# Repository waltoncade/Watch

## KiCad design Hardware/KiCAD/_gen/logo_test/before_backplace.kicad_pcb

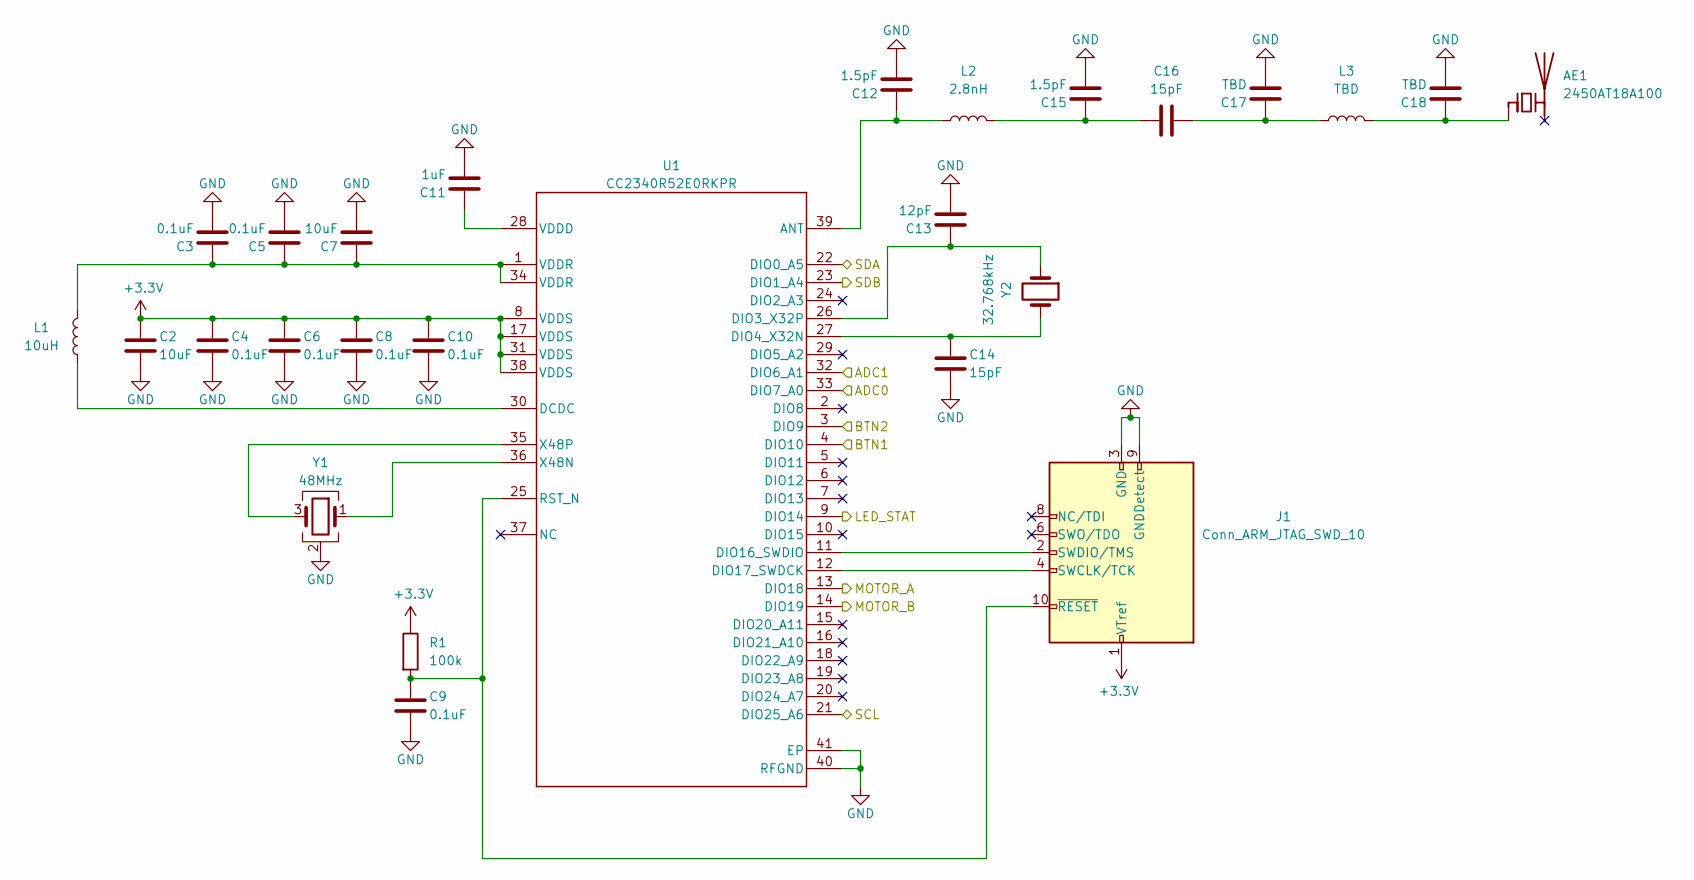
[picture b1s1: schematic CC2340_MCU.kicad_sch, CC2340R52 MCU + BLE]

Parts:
AE1: 2450AT18A100; Johanson_2450AT18x100; MPN Johanson 2450AT18A100 (placeholder, TBD)
C2, C7: 10uF; C_0402_1005Metric
C3, C4, C5, C6, C8, C9, C10: 0.1uF; C_0402_1005Metric
C11: 1uF; C_0402_1005Metric
C12, C15: 1.5pF; C_0402_1005Metric
C13: 12pF; C_0402_1005Metric
C14, C16: 15pF; C_0402_1005Metric
C17, C18: TBD; C_0402_1005Metric
J1: Conn_ARM_JTAG_SWD_10; PinHeader_2x05_P1.27mm_Vertical_SMD
L1: 10uH; L_0603_1608Metric; MPN MLZ1608N100LT000 (TI E2E-tested 0603 al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
L2: 2.8nH; L_0402_1005Metric
L3: TBD; L_0402_1005Metric
R1: 100k; R_0402_1005Metric
U1: CC2340R52E0RKPR; RKP0040B-IPC_B
Y1: 48MHz; Crystal_SMD_2016-4Pin_2.0x1.6mm; MPN TZ3908AAAO43
Y2: 32.768kHz; Crystal_SMD_2012-2Pin_2.0x1.2mm; MPN TBD (CL 6-12pF per SWRS272F CC2340R5 da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

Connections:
+3.3V: C2.1, C4.1, C6.1, C8.1, C10.1, J1.1 (VTref), R1.1, U1.8 (VDDS), U1.17 (VDDS), U1.31 (VDDS), U1.38 (VDDS); also elsewhere on the board
/ACC_INT: U1.20 (DIO24_A7); also elsewhere on the board
/LED_EN: U1.23 (DIO1_A4); also elsewhere on the board
/MCU/LED_STAT: U1.9 (DIO14); also elsewhere on the board
/MCU/MOTOR_A: U1.13 (DIO18); also elsewhere on the board
/MCU/MOTOR_B: U1.14 (DIO19); also elsewhere on the board
/SW1: U1.4 (DIO10); also elsewhere on the board
/SW2: U1.3 (DIO9); also elsewhere on the board
/bSense: U1.33 (DIO7_A0); also elsewhere on the board
/leds/SCL: U1.21 (DIO25_A6); also elsewhere on the board
/leds/SDA: U1.22 (DIO0_A5); also elsewhere on the board
/vLUX: U1.32 (DIO6_A1); also elsewhere on the board
GND: C2.2, C3.2, C4.2, C5.2, C6.2, C7.2, C8.2, C9.2, C10.2, C11.2, C12.2, C13.2, C14.2, C15.2, C17.2, C18.2, J1.3 (GND), J1.5 (GND), J1.9 (GNDDetect), U1.40 (RFGND), U1.41 (EP), Y1.2 (G), Y1.4 (G); also elsewhere on the board
unnamed: AE1.1 (FEED_1), C18.1, L3.2
unnamed: C3.1, C5.1, C7.1, L1.2, U1.1 (VDDR), U1.34 (VDDR)
unnamed: C15.1, C16.1, L2.2
unnamed: C16.2, C17.1, L3.1
unnamed 50: J1.4 (SWCLK/TCK), U1.12 (DIO17_SWDCK); also elsewhere on the board
unnamed 51: J1.2 (SWDIO/TMS), U1.11 (DIO16_SWDIO); also elsewhere on the board
unnamed: C12.1, L2.1, U1.39 (ANT)
unnamed: L1.1, U1.30 (DCDC)
unnamed: C13.1, U1.26 (DIO3_X32P), Y2.1
unnamed: C14.1, U1.27 (DIO4_X32N), Y2.2
unnamed: C11.1, U1.28 (VDDD)
unnamed: U1.36 (X48N), Y1.1
unnamed: U1.35 (X48P), Y1.3

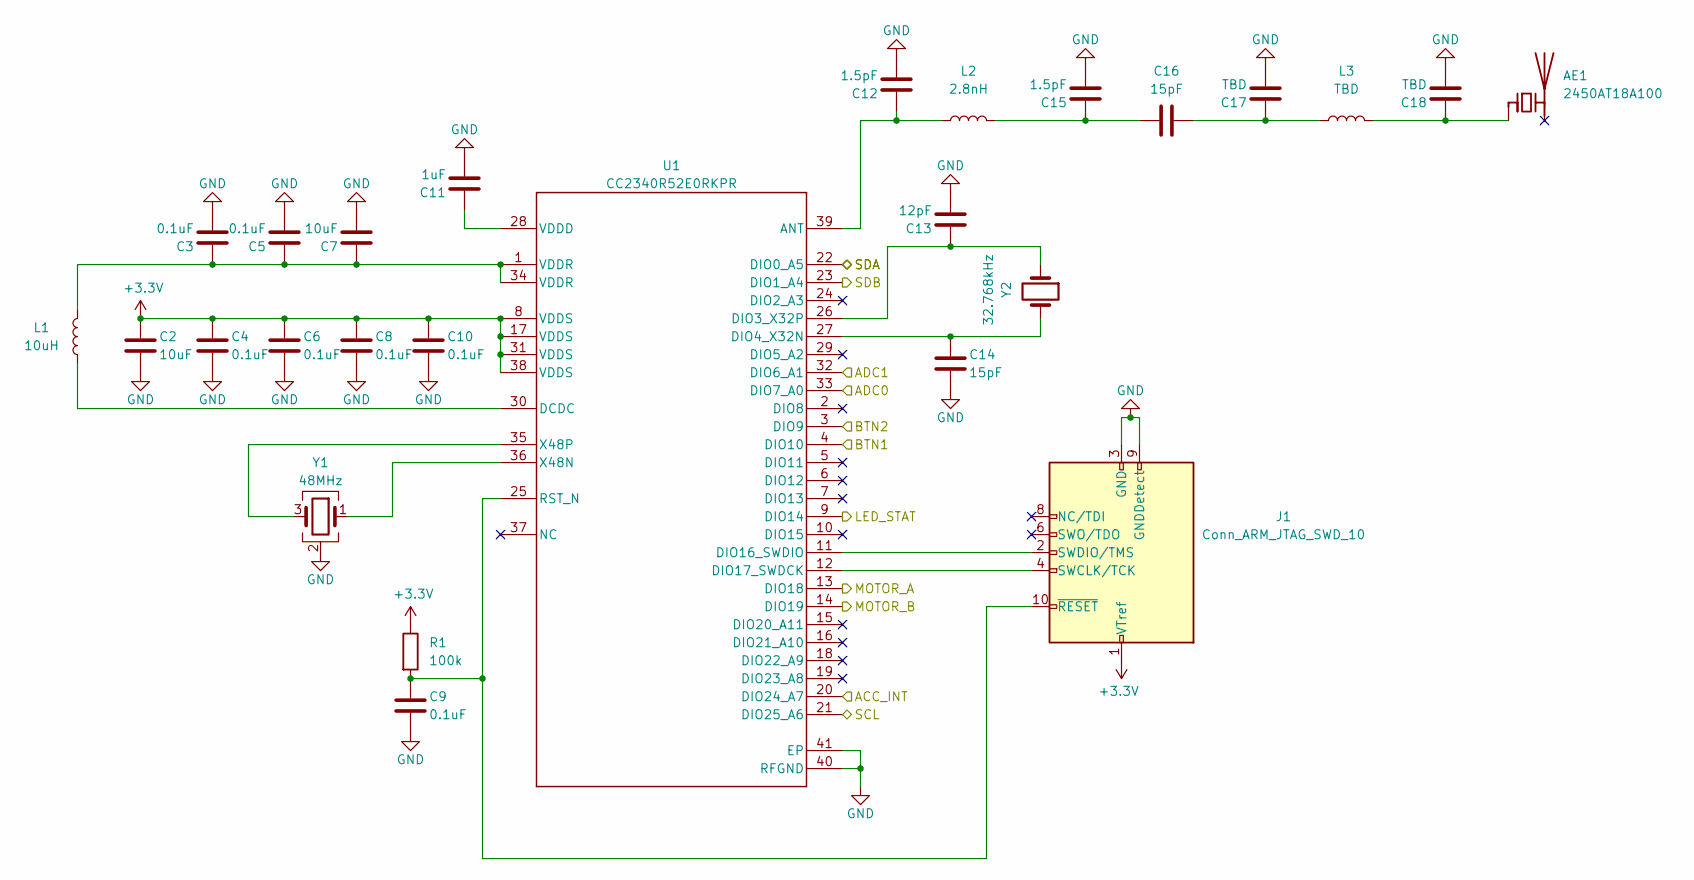
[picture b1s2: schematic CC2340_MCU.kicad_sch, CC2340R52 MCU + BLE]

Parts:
AE1: 2450AT18A100; Johanson_2450AT18x100; MPN Johanson 2450AT18A100 (placeholder, TBD)
C2, C7: 10uF; C_0402_1005Metric
C3, C4, C5, C6, C8, C9, C10: 0.1uF; C_0402_1005Metric
C11: 1uF; C_0402_1005Metric
C12, C15: 1.5pF; C_0402_1005Metric
C13: 12pF; C_0402_1005Metric
C14, C16: 15pF; C_0402_1005Metric
C17, C18: TBD; C_0402_1005Metric
J1: Conn_ARM_JTAG_SWD_10; PinHeader_2x05_P1.27mm_Vertical_SMD
L1: 10uH; L_0603_1608Metric; MPN MLZ1608N100LT000 (TI E2E-tested 0603 al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
L2: 2.8nH; L_0402_1005Metric
L3: TBD; L_0402_1005Metric
R1: 100k; R_0402_1005Metric
U1: CC2340R52E0RKPR; RKP0040B-IPC_B
Y1: 48MHz; Crystal_SMD_2016-4Pin_2.0x1.6mm; MPN TZ3908AAAO43
Y2: 32.768kHz; Crystal_SMD_2012-2Pin_2.0x1.2mm; MPN TBD (CL 6-12pF per SWRS272F CC2340R5 da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

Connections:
+3.3V: C2.1, C4.1, C6.1, C8.1, C10.1, J1.1 (VTref), R1.1, U1.8 (VDDS), U1.17 (VDDS), U1.31 (VDDS), U1.38 (VDDS); also elsewhere on the board
/ACC_INT: U1.20 (DIO24_A7); also elsewhere on the board
/LED_EN: U1.23 (DIO1_A4); also elsewhere on the board
/MCU/LED_STAT: U1.9 (DIO14); also elsewhere on the board
/MCU/MOTOR_A: U1.13 (DIO18); also elsewhere on the board
/MCU/MOTOR_B: U1.14 (DIO19); also elsewhere on the board
/SW1: U1.4 (DIO10); also elsewhere on the board
/SW2: U1.3 (DIO9); also elsewhere on the board
/bSense: U1.33 (DIO7_A0); also elsewhere on the board
/leds/SCL: U1.21 (DIO25_A6); also elsewhere on the board
/leds/SDA: U1.22 (DIO0_A5); also elsewhere on the board
/vLUX: U1.32 (DIO6_A1); also elsewhere on the board
GND: C2.2, C3.2, C4.2, C5.2, C6.2, C7.2, C8.2, C9.2, C10.2, C11.2, C12.2, C13.2, C14.2, C15.2, C17.2, C18.2, J1.3 (GND), J1.5 (GND), J1.9 (GNDDetect), U1.40 (RFGND), U1.41 (EP), Y1.2 (G), Y1.4 (G); also elsewhere on the board
unnamed: AE1.1 (FEED_1), C18.1, L3.2
unnamed: C3.1, C5.1, C7.1, L1.2, U1.1 (VDDR), U1.34 (VDDR)
unnamed: C15.1, C16.1, L2.2
unnamed: C16.2, C17.1, L3.1
unnamed 50: J1.4 (SWCLK/TCK), U1.12 (DIO17_SWDCK); also elsewhere on the board
unnamed 51: J1.2 (SWDIO/TMS), U1.11 (DIO16_SWDIO); also elsewhere on the board
unnamed: C12.1, L2.1, U1.39 (ANT)
unnamed: L1.1, U1.30 (DCDC)
unnamed: C13.1, U1.26 (DIO3_X32P), Y2.1
unnamed: C14.1, U1.27 (DIO4_X32N), Y2.2
unnamed: C11.1, U1.28 (VDDD)
unnamed: U1.36 (X48N), Y1.1
unnamed: U1.35 (X48P), Y1.3

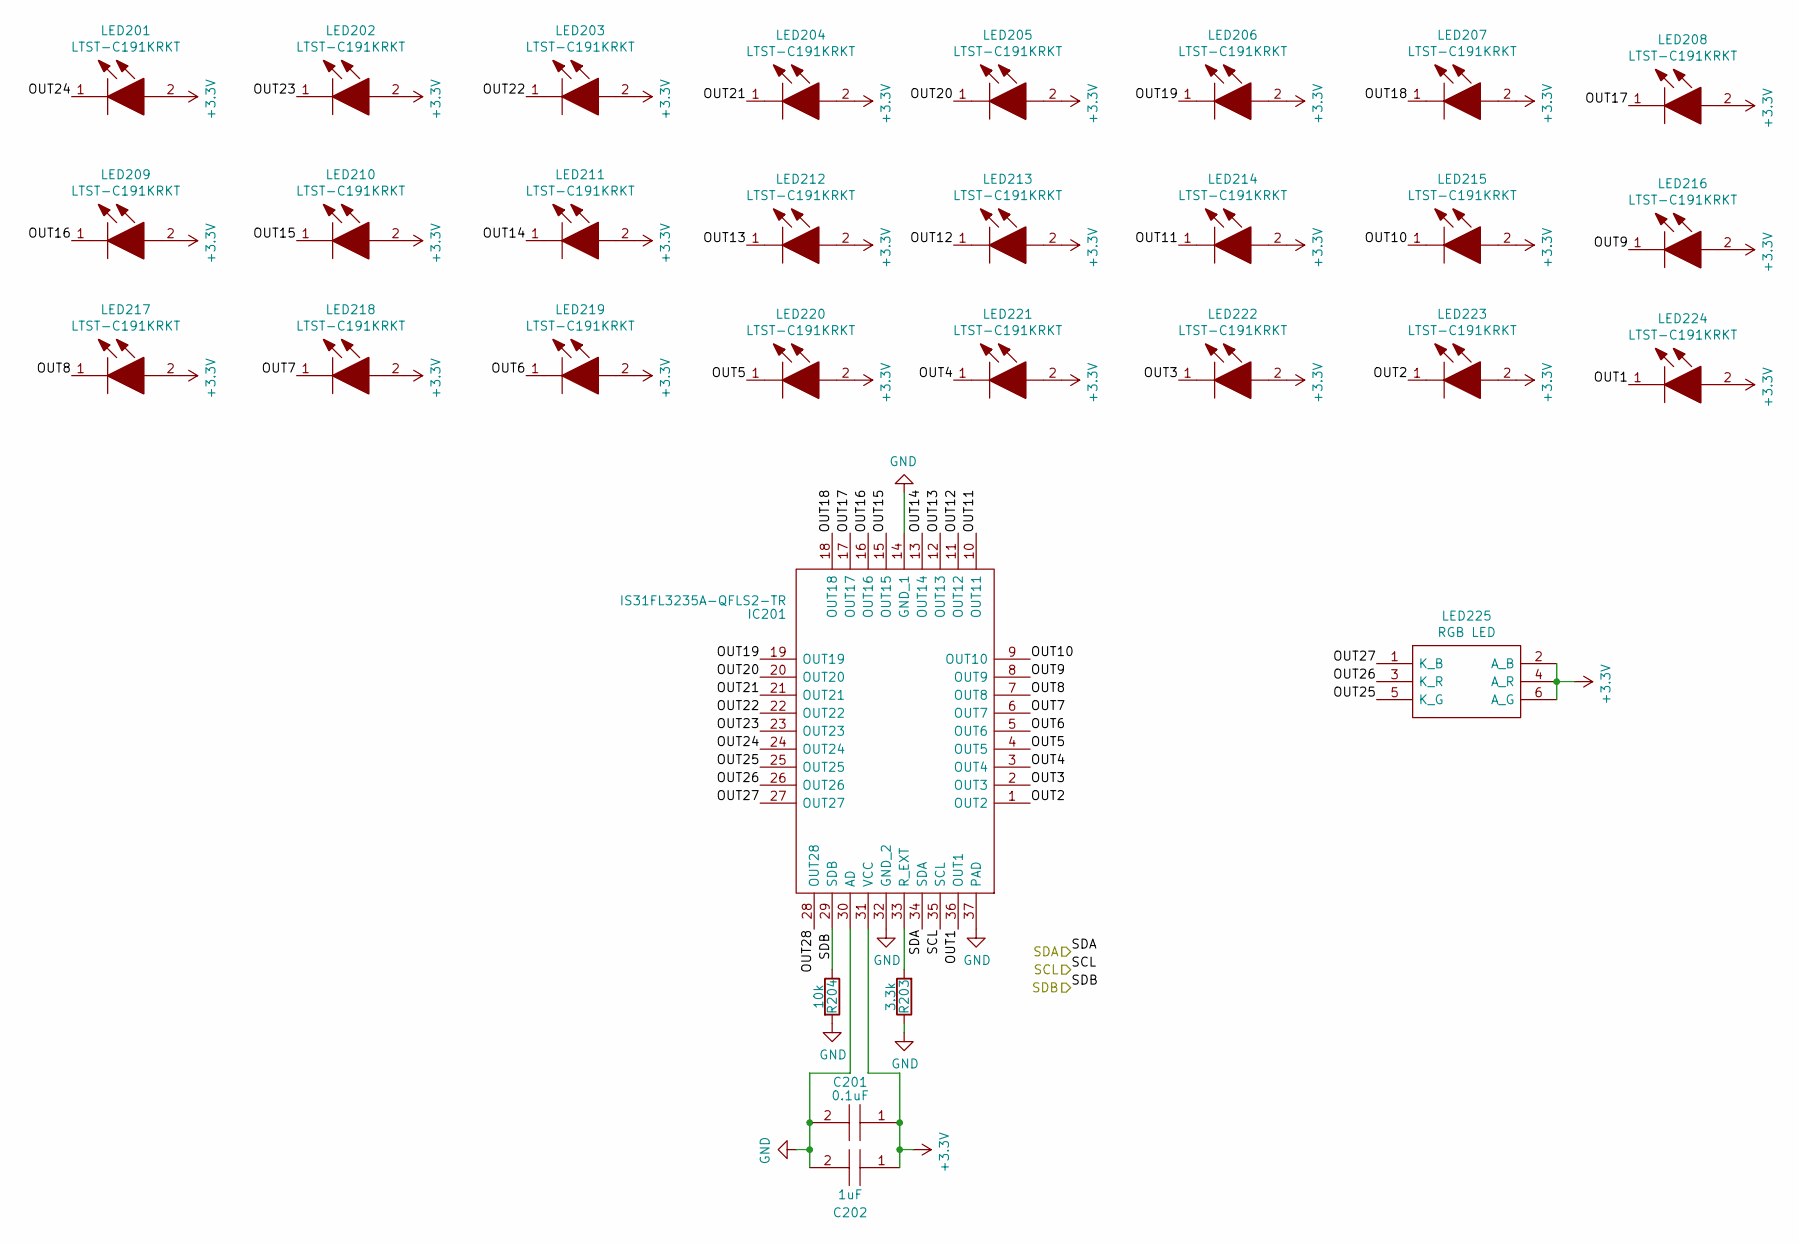
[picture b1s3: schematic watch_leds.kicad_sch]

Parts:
C201: 0.1uF; CAPC1005X55N; Manufacturer_Part_Number CL05A104KA5NNNC; Mouser Part Number 187-CL05A104KA5NNNC
C202: 1uF; CAPC1005X55N; Manufacturer_Part_Number CL05A105KQ5NNNC; Mouser Part Number 187-CL05A105KQ5NNNC
IC201: IS31FL3235A-QFLS2-TR; QFN40P400X400X80-37N; Manufacturer_Part_Number IS31FL3235A-QFLS2-TR; Mouser Part Number 870-31FL3235AQFLS2T
LED201, LED202, LED203, LED204, LED205, LED206, LED207, LED208, LED209, LED210, LED211, LED212, LED213, LED214, LED215, LED216, LED217, LED218, LED219, LED220, LED221, LED222, LED223, LED224: LTST-C191KRKT; LEDC1608X55N; Manufacturer_Part_Number LTST-C191KRKT; Mouser Part Number 859-LTST-C191KRKT
LED225: RGB LED; 150352M173300; Mouser Part Number 710-150352M173300
R203: 3.3k; R_0402_1005Metric
R204: 10k; R_0402_1005Metric

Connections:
+3.3V: C201.1, C202.1, IC201.31 (VCC), LED201.2, LED202.2, LED203.2, LED204.2, LED205.2, LED206.2, LED207.2, LED208.2, LED209.2, LED210.2, LED211.2, LED212.2, LED213.2, LED214.2, LED215.2, LED216.2, LED217.2, LED218.2, LED219.2, LED220.2, LED221.2, LED222.2, LED223.2, LED224.2, LED225.2 (A_B), LED225.4 (A_R), LED225.6 (A_G); also elsewhere on the board
/LED_EN: IC201.29 (SDB), R204.1; also elsewhere on the board
/leds/OUT1: IC201.36 (OUT1), LED224.1
/leds/OUT2: IC201.1 (OUT2), LED223.1
/leds/OUT3: IC201.2 (OUT3), LED222.1
/leds/OUT4: IC201.3 (OUT4), LED221.1
/leds/OUT5: IC201.4 (OUT5), LED220.1
/leds/OUT6: IC201.5 (OUT6), LED219.1
/leds/OUT7: IC201.6 (OUT7), LED218.1
/leds/OUT8: IC201.7 (OUT8), LED217.1
/leds/OUT9: IC201.8 (OUT9), LED216.1
/leds/OUT10: IC201.9 (OUT10), LED215.1
/leds/OUT11: IC201.10 (OUT11), LED214.1
/leds/OUT12: IC201.11 (OUT12), LED213.1
/leds/OUT13: IC201.12 (OUT13), LED212.1
/leds/OUT14: IC201.13 (OUT14), LED211.1
/leds/OUT15: IC201.15 (OUT15), LED210.1
/leds/OUT16: IC201.16 (OUT16), LED209.1
/leds/OUT17: IC201.17 (OUT17), LED208.1
/leds/OUT18: IC201.18 (OUT18), LED207.1
/leds/OUT19: IC201.19 (OUT19), LED206.1
/leds/OUT20: IC201.20 (OUT20), LED205.1
/leds/OUT21: IC201.21 (OUT21), LED204.1
/leds/OUT22: IC201.22 (OUT22), LED203.1
/leds/OUT23: IC201.23 (OUT23), LED202.1
/leds/OUT24: IC201.24 (OUT24), LED201.1
/leds/OUT25: IC201.25 (OUT25), LED225.5 (K_G)
/leds/OUT26: IC201.26 (OUT26), LED225.3 (K_R)
/leds/OUT27: IC201.27 (OUT27), LED225.1 (K_B)
/leds/OUT28: IC201.28 (OUT28)
/leds/SCL: IC201.35 (SCL); also elsewhere on the board
/leds/SDA: IC201.34 (SDA); also elsewhere on the board
GND: C201.2, C202.2, IC201.14 (GND_1), IC201.30 (AD), IC201.32 (GND_2), IC201.37 (PAD), R203.1, R204.2; also elsewhere on the board
unnamed: IC201.33 (R_EXT), R203.2

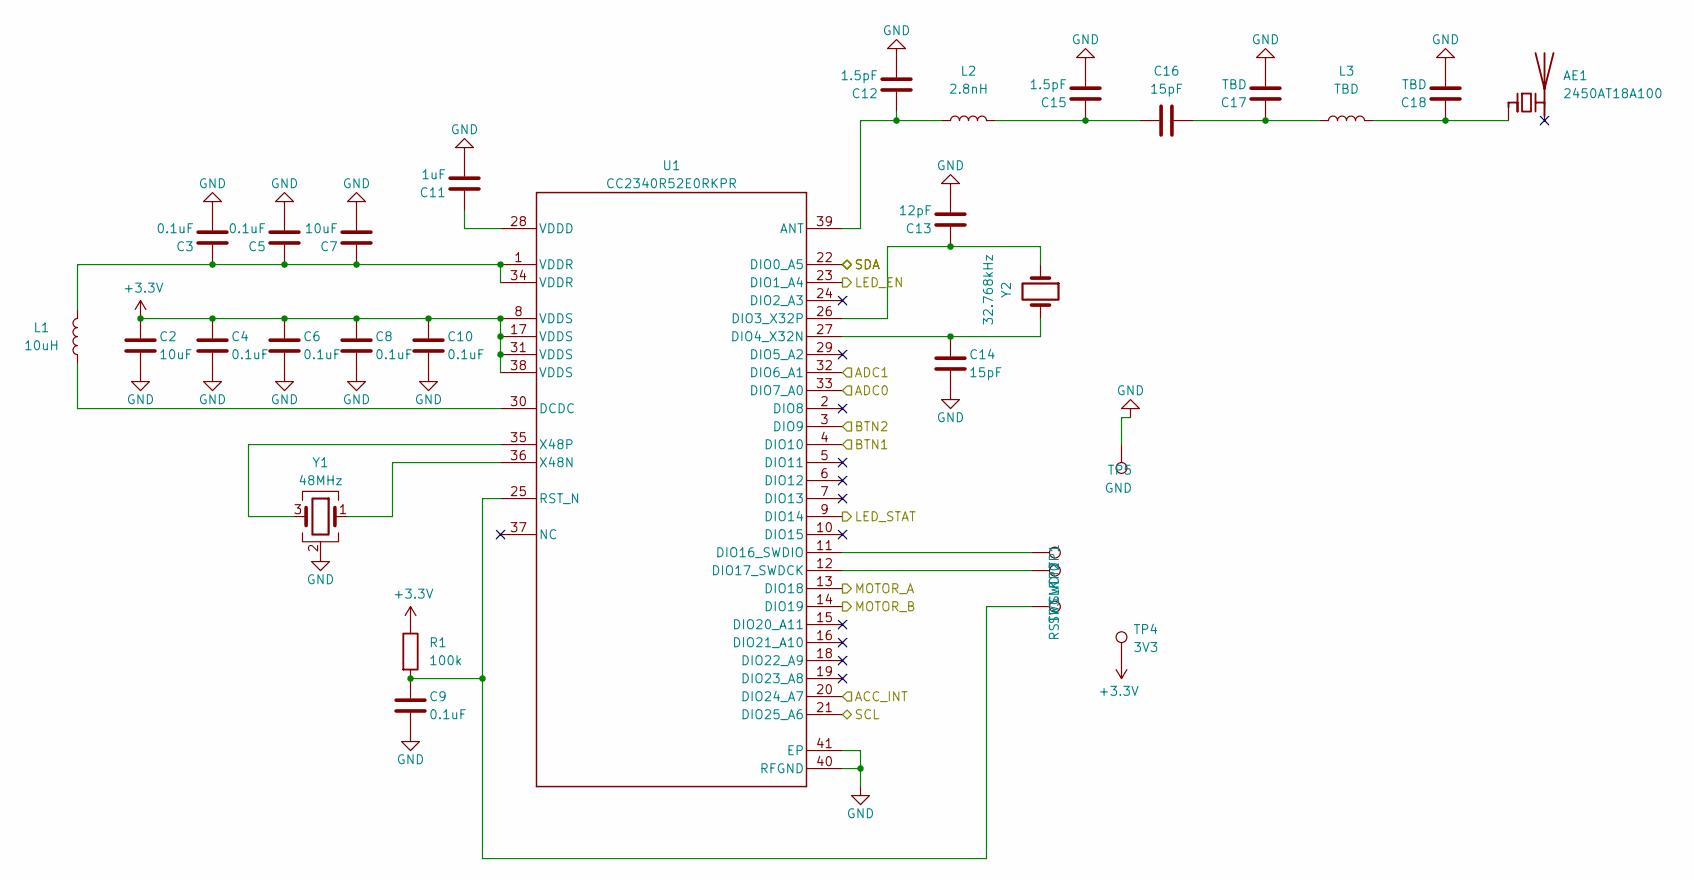
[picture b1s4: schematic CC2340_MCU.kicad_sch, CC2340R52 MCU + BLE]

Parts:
AE1: 2450AT18A100; Johanson_2450AT18x100; MPN Johanson 2450AT18A100 (placeholder, TBD)
C2, C7: 10uF; C_0402_1005Metric
C3, C4, C5, C6, C8, C9, C10: 0.1uF; C_0402_1005Metric
C11: 1uF; C_0402_1005Metric
C12, C15: 1.5pF; C_0402_1005Metric
C13: 12pF; C_0402_1005Metric
C14, C16: 15pF; C_0402_1005Metric
C17, C18: TBD; C_0402_1005Metric
L1: 10uH; L_0603_1608Metric; MPN MLZ1608N100LT000 (TI E2E-tested 0603 al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
L2: 2.8nH; L_0402_1005Metric
L3: TBD; L_0402_1005Metric
R1: 100k; R_0402_1005Metric
TP1: SWDIO; TestPoint_Pad_D1.0mm
TP2: SWCLK; TestPoint_Pad_D1.0mm
TP3: RST; TestPoint_Pad_D1.0mm
TP4: 3V3; TestPoint_Pad_D1.0mm
TP5: GND; TestPoint_Pad_D1.0mm
U1: CC2340R52E0RKPR; RKP0040B-IPC_B
Y1: 48MHz; Crystal_SMD_2016-4Pin_2.0x1.6mm; MPN TZ3908AAAO43
Y2: 32.768kHz; Crystal_SMD_2012-2Pin_2.0x1.2mm; MPN TBD (CL 6-12pF per SWRS272F CC2340R5 da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

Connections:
+3.3V: C2.1, C4.1, C6.1, C8.1, C10.1, R1.1, TP4.1, U1.8 (VDDS), U1.17 (VDDS), U1.31 (VDDS), U1.38 (VDDS); also elsewhere on the board
/ACC_INT: U1.20 (DIO24_A7); also elsewhere on the board
/LED_EN: U1.23 (DIO1_A4); also elsewhere on the board
/MCU/LED_STAT: U1.9 (DIO14); also elsewhere on the board
/MCU/MOTOR_A: U1.13 (DIO18); also elsewhere on the board
/MCU/MOTOR_B: U1.14 (DIO19); also elsewhere on the board
/SW1: U1.4 (DIO10); also elsewhere on the board
/SW2: U1.3 (DIO9); also elsewhere on the board
/bSense: U1.33 (DIO7_A0); also elsewhere on the board
/leds/SCL: U1.21 (DIO25_A6); also elsewhere on the board
/leds/SDA: U1.22 (DIO0_A5); also elsewhere on the board
/vLUX: U1.32 (DIO6_A1); also elsewhere on the board
GND: C2.2, C3.2, C4.2, C5.2, C6.2, C7.2, C8.2, C9.2, C10.2, C11.2, C12.2, C13.2, C14.2, C15.2, C17.2, C18.2, TP5.1, U1.40 (RFGND), U1.41 (EP), Y1.2 (G), Y1.4 (G); also elsewhere on the board
unnamed: AE1.1 (FEED_1), C18.1, L3.2
unnamed: C3.1, C5.1, C7.1, L1.2, U1.1 (VDDR), U1.34 (VDDR)
unnamed: C15.1, C16.1, L2.2
unnamed: C16.2, C17.1, L3.1
unnamed 50: TP2.1, U1.12 (DIO17_SWDCK); also elsewhere on the board
unnamed 51: TP1.1, U1.11 (DIO16_SWDIO); also elsewhere on the board
unnamed: C12.1, L2.1, U1.39 (ANT)
unnamed: L1.1, U1.30 (DCDC)
unnamed: C13.1, U1.26 (DIO3_X32P), Y2.1
unnamed: C14.1, U1.27 (DIO4_X32N), Y2.2
unnamed: C11.1, U1.28 (VDDD)
unnamed: U1.36 (X48N), Y1.1
unnamed: U1.35 (X48P), Y1.3

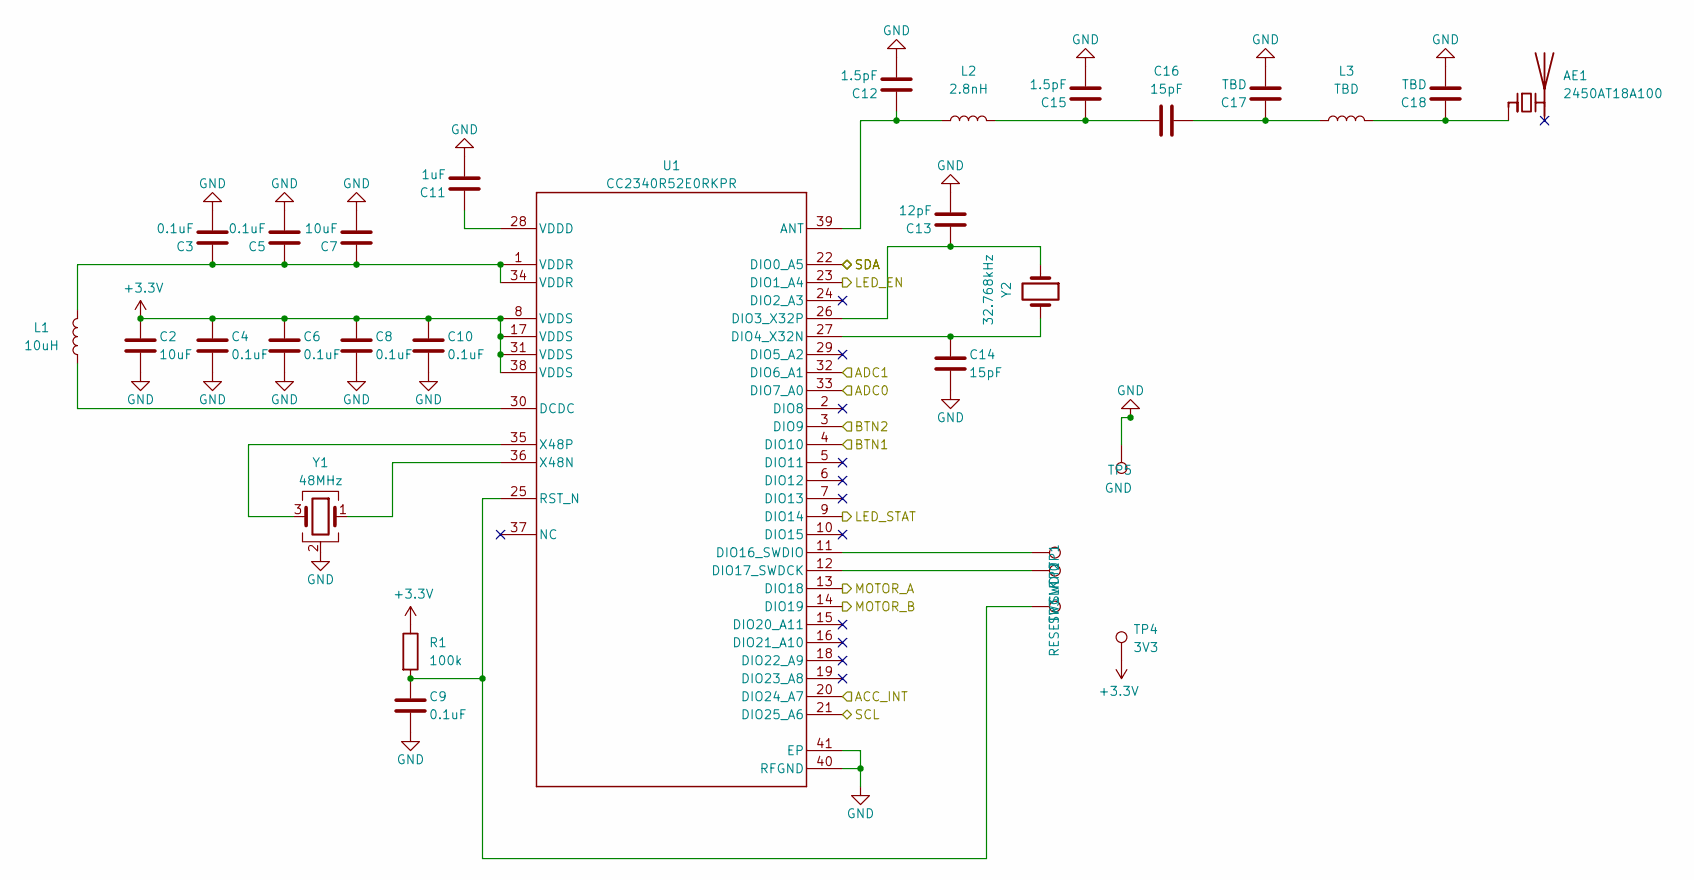
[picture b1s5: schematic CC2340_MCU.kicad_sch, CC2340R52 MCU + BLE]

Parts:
AE1: 2450AT18A100; Johanson_2450AT18x100; MPN Johanson 2450AT18A100 (placeholder, TBD)
C2, C7: 10uF; C_0402_1005Metric
C3, C4, C5, C6, C8, C9, C10: 0.1uF; C_0402_1005Metric
C11: 1uF; C_0402_1005Metric
C12, C15: 1.5pF; C_0402_1005Metric
C13: 12pF; C_0402_1005Metric
C14, C16: 15pF; C_0402_1005Metric
C17, C18: TBD; C_0402_1005Metric
L1: 10uH; L_0603_1608Metric; MPN MLZ1608N100LT000 (TI E2E-tested 0603 al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
L2: 2.8nH; L_0402_1005Metric
L3: TBD; L_0402_1005Metric
R1: 100k; R_0402_1005Metric
TP1: SWDIO; TestPoint_Pad_D1.0mm
TP2: SWCLK; TestPoint_Pad_D1.0mm
TP3: RESET; TestPoint_Pad_D1.0mm
TP4: 3V3; TestPoint_Pad_D1.0mm
TP5: GND; TestPoint_Pad_D1.0mm
U1: CC2340R52E0RKPR; RKP0040B-IPC_B
Y1: 48MHz; Crystal_SMD_2016-4Pin_2.0x1.6mm; MPN TZ3908AAAO43
Y2: 32.768kHz; Crystal_SMD_2012-2Pin_2.0x1.2mm; MPN TBD (CL 6-12pF per SWRS272F CC2340R5 da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

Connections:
+3.3V: C2.1, C4.1, C6.1, C8.1, C10.1, R1.1, TP4.1, U1.8 (VDDS), U1.17 (VDDS), U1.31 (VDDS), U1.38 (VDDS); also elsewhere on the board
/ACC_INT: U1.20 (DIO24_A7); also elsewhere on the board
/LED_EN: U1.23 (DIO1_A4); also elsewhere on the board
/MCU/LED_STAT: U1.9 (DIO14); also elsewhere on the board
/MCU/MOTOR_A: U1.13 (DIO18); also elsewhere on the board
/MCU/MOTOR_B: U1.14 (DIO19); also elsewhere on the board
/SW1: U1.4 (DIO10); also elsewhere on the board
/SW2: U1.3 (DIO9); also elsewhere on the board
/bSense: U1.33 (DIO7_A0); also elsewhere on the board
/leds/SCL: U1.21 (DIO25_A6); also elsewhere on the board
/leds/SDA: U1.22 (DIO0_A5); also elsewhere on the board
/vLUX: U1.32 (DIO6_A1); also elsewhere on the board
GND: C2.2, C3.2, C4.2, C5.2, C6.2, C7.2, C8.2, C9.2, C10.2, C11.2, C12.2, C13.2, C14.2, C15.2, C17.2, C18.2, TP5.1, U1.40 (RFGND), U1.41 (EP), Y1.2 (G), Y1.4 (G); also elsewhere on the board
unnamed: AE1.1 (FEED_1), C18.1, L3.2
unnamed: C3.1, C5.1, C7.1, L1.2, U1.1 (VDDR), U1.34 (VDDR)
unnamed: C15.1, C16.1, L2.2
unnamed: C16.2, C17.1, L3.1
unnamed 50: TP2.1, U1.12 (DIO17_SWDCK); also elsewhere on the board
unnamed 51: TP1.1, U1.11 (DIO16_SWDIO); also elsewhere on the board
unnamed: C12.1, L2.1, U1.39 (ANT)
unnamed: L1.1, U1.30 (DCDC)
unnamed: C13.1, U1.26 (DIO3_X32P), Y2.1
unnamed: C14.1, U1.27 (DIO4_X32N), Y2.2
unnamed: C11.1, U1.28 (VDDD)
unnamed: U1.36 (X48N), Y1.1
unnamed: U1.35 (X48P), Y1.3

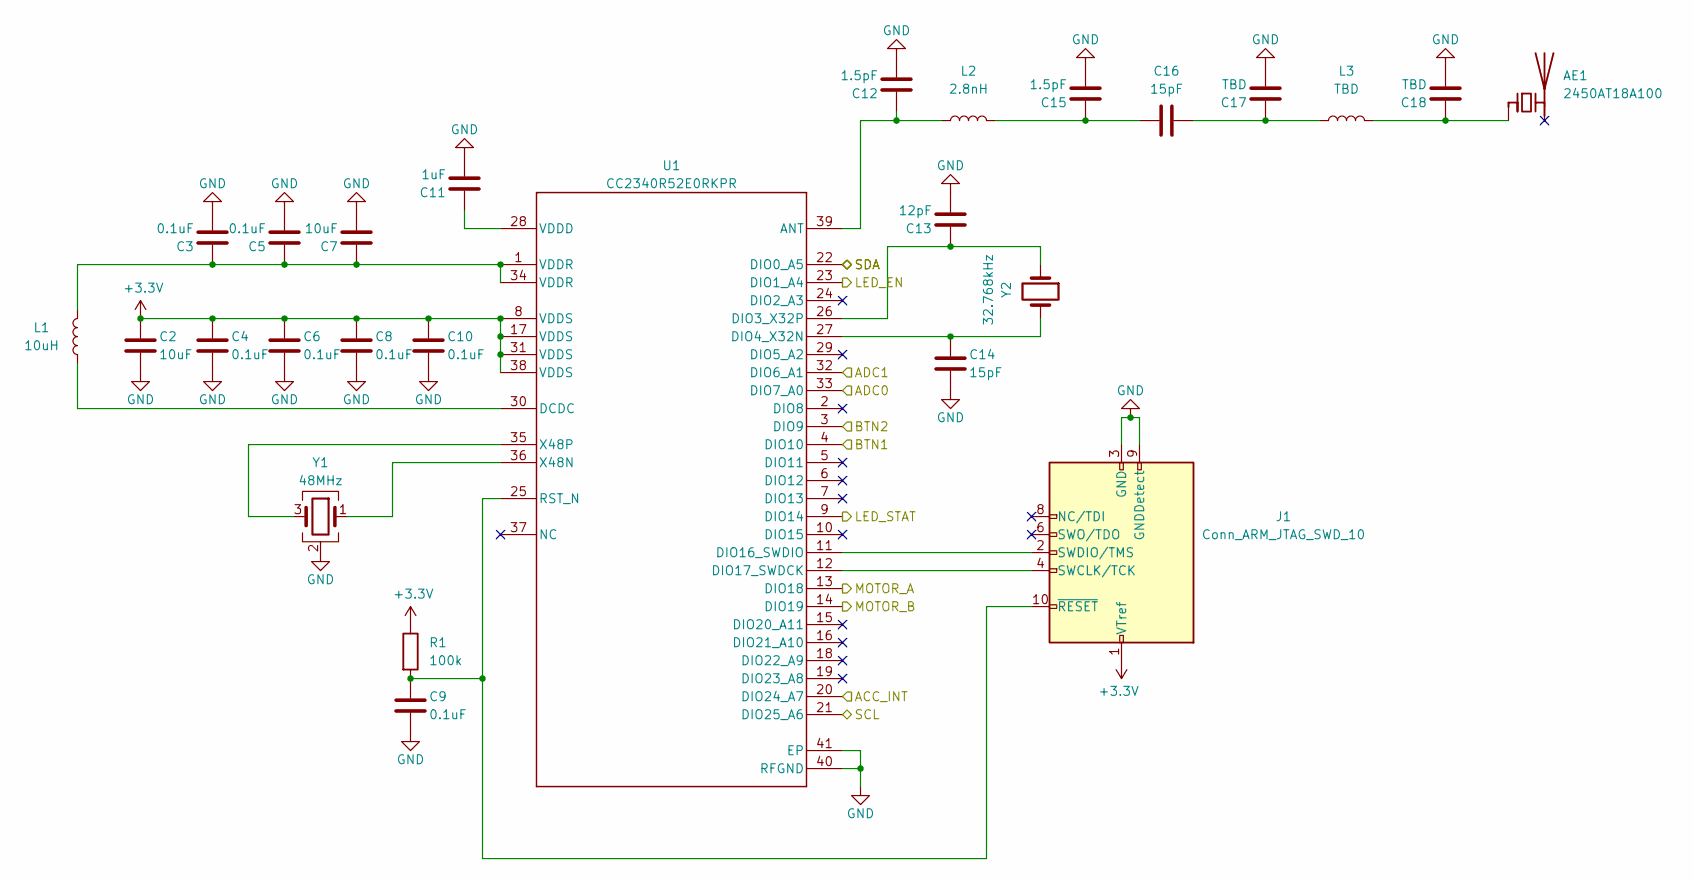
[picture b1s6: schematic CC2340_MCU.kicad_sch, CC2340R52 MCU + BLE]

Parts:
AE1: 2450AT18A100; Johanson_2450AT18x100; MPN Johanson 2450AT18A100 (placeholder, TBD)
C2, C7: 10uF; C_0402_1005Metric
C3, C4, C5, C6, C8, C9, C10: 0.1uF; C_0402_1005Metric
C11: 1uF; C_0402_1005Metric
C12, C15: 1.5pF; C_0402_1005Metric
C13: 12pF; C_0402_1005Metric
C14, C16: 15pF; C_0402_1005Metric
C17, C18: TBD; C_0402_1005Metric
J1: Conn_ARM_JTAG_SWD_10; PinHeader_2x05_P1.27mm_Vertical_SMD
L1: 10uH; L_0603_1608Metric; MPN MLZ1608N100LT000 (TI E2E-tested 0603 al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
L2: 2.8nH; L_0402_1005Metric
L3: TBD; L_0402_1005Metric
R1: 100k; R_0402_1005Metric
U1: CC2340R52E0RKPR; RKP0040B-IPC_B
Y1: 48MHz; Crystal_SMD_2016-4Pin_2.0x1.6mm; MPN TZ3908AAAO43
Y2: 32.768kHz; Crystal_SMD_2012-2Pin_2.0x1.2mm; MPN TBD (CL 6-12pF per SWRS272F CC2340R5 da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

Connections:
+3.3V: C2.1, C4.1, C6.1, C8.1, C10.1, J1.1 (VTref), R1.1, U1.8 (VDDS), U1.17 (VDDS), U1.31 (VDDS), U1.38 (VDDS); also elsewhere on the board
/ACC_INT: U1.20 (DIO24_A7); also elsewhere on the board
/LED_EN: U1.23 (DIO1_A4); also elsewhere on the board
/MCU/LED_STAT: U1.9 (DIO14); also elsewhere on the board
/MCU/MOTOR_A: U1.13 (DIO18); also elsewhere on the board
/MCU/MOTOR_B: U1.14 (DIO19); also elsewhere on the board
/SW1: U1.4 (DIO10); also elsewhere on the board
/SW2: U1.3 (DIO9); also elsewhere on the board
/bSense: U1.33 (DIO7_A0); also elsewhere on the board
/leds/SCL: U1.21 (DIO25_A6); also elsewhere on the board
/leds/SDA: U1.22 (DIO0_A5); also elsewhere on the board
/vLUX: U1.32 (DIO6_A1); also elsewhere on the board
GND: C2.2, C3.2, C4.2, C5.2, C6.2, C7.2, C8.2, C9.2, C10.2, C11.2, C12.2, C13.2, C14.2, C15.2, C17.2, C18.2, J1.3 (GND), J1.5 (GND), J1.9 (GNDDetect), U1.40 (RFGND), U1.41 (EP), Y1.2 (G), Y1.4 (G); also elsewhere on the board
unnamed: AE1.1 (FEED_1), C18.1, L3.2
unnamed: C3.1, C5.1, C7.1, L1.2, U1.1 (VDDR), U1.34 (VDDR)
unnamed: C15.1, C16.1, L2.2
unnamed: C16.2, C17.1, L3.1
unnamed 50: J1.4 (SWCLK/TCK), U1.12 (DIO17_SWDCK); also elsewhere on the board
unnamed 51: J1.2 (SWDIO/TMS), U1.11 (DIO16_SWDIO); also elsewhere on the board
unnamed: C12.1, L2.1, U1.39 (ANT)
unnamed: L1.1, U1.30 (DCDC)
unnamed: C13.1, U1.26 (DIO3_X32P), Y2.1
unnamed: C14.1, U1.27 (DIO4_X32N), Y2.2
unnamed: C11.1, U1.28 (VDDD)
unnamed: U1.36 (X48N), Y1.1
unnamed: U1.35 (X48P), Y1.3

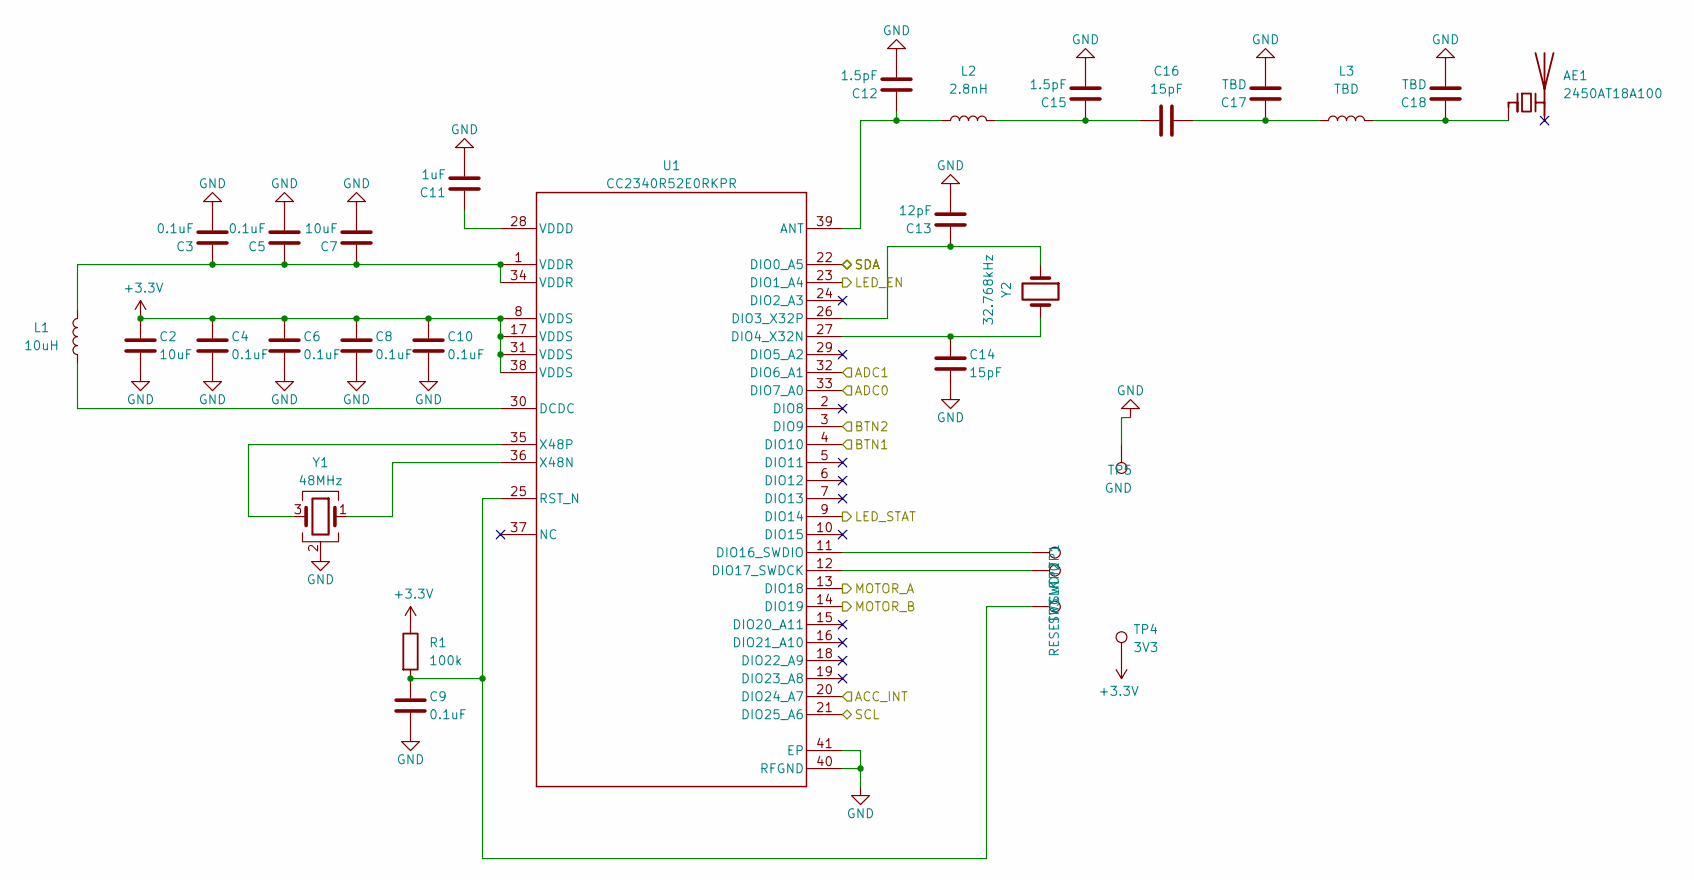
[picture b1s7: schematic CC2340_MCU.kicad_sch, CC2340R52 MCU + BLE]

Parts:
AE1: 2450AT18A100; Johanson_2450AT18x100; MPN Johanson 2450AT18A100 (placeholder, TBD)
C2, C7: 10uF; C_0402_1005Metric
C3, C4, C5, C6, C8, C9, C10: 0.1uF; C_0402_1005Metric
C11: 1uF; C_0402_1005Metric
C12, C15: 1.5pF; C_0402_1005Metric
C13: 12pF; C_0402_1005Metric
C14, C16: 15pF; C_0402_1005Metric
C17, C18: TBD; C_0402_1005Metric
L1: 10uH; L_0603_1608Metric; MPN MLZ1608N100LT000 (TI E2E-tested 0603 al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
L2: 2.8nH; L_0402_1005Metric
L3: TBD; L_0402_1005Metric
R1: 100k; R_0402_1005Metric
TP1: SWDIO; TestPoint_Pad_D1.0mm
TP2: SWCLK; TestPoint_Pad_D1.0mm
TP3: RESET; TestPoint_Pad_D1.0mm
TP4: 3V3; TestPoint_Pad_D1.0mm
TP5: GND; TestPoint_Pad_D1.0mm
U1: CC2340R52E0RKPR; RKP0040B-IPC_B
Y1: 48MHz; Crystal_SMD_2016-4Pin_2.0x1.6mm; MPN TZ3908AAAO43
Y2: 32.768kHz; Crystal_SMD_2012-2Pin_2.0x1.2mm; MPN TBD (CL 6-12pF per SWRS272F CC2340R5 da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

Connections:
+3.3V: C2.1, C4.1, C6.1, C8.1, C10.1, R1.1, TP4.1, U1.8 (VDDS), U1.17 (VDDS), U1.31 (VDDS), U1.38 (VDDS); also elsewhere on the board
/ACC_INT: U1.20 (DIO24_A7); also elsewhere on the board
/LED_EN: U1.23 (DIO1_A4); also elsewhere on the board
/MCU/LED_STAT: U1.9 (DIO14); also elsewhere on the board
/MCU/MOTOR_A: U1.13 (DIO18); also elsewhere on the board
/MCU/MOTOR_B: U1.14 (DIO19); also elsewhere on the board
/SW1: U1.4 (DIO10); also elsewhere on the board
/SW2: U1.3 (DIO9); also elsewhere on the board
/bSense: U1.33 (DIO7_A0); also elsewhere on the board
/leds/SCL: U1.21 (DIO25_A6); also elsewhere on the board
/leds/SDA: U1.22 (DIO0_A5); also elsewhere on the board
/vLUX: U1.32 (DIO6_A1); also elsewhere on the board
GND: C2.2, C3.2, C4.2, C5.2, C6.2, C7.2, C8.2, C9.2, C10.2, C11.2, C12.2, C13.2, C14.2, C15.2, C17.2, C18.2, TP5.1, U1.40 (RFGND), U1.41 (EP), Y1.2 (G), Y1.4 (G); also elsewhere on the board
unnamed: AE1.1 (FEED_1), C18.1, L3.2
unnamed: C3.1, C5.1, C7.1, L1.2, U1.1 (VDDR), U1.34 (VDDR)
unnamed: C15.1, C16.1, L2.2
unnamed: C16.2, C17.1, L3.1
unnamed 50: TP2.1, U1.12 (DIO17_SWDCK); also elsewhere on the board
unnamed 51: TP1.1, U1.11 (DIO16_SWDIO); also elsewhere on the board
unnamed: C12.1, L2.1, U1.39 (ANT)
unnamed: L1.1, U1.30 (DCDC)
unnamed: C13.1, U1.26 (DIO3_X32P), Y2.1
unnamed: C14.1, U1.27 (DIO4_X32N), Y2.2
unnamed: C11.1, U1.28 (VDDD)
unnamed: U1.36 (X48N), Y1.1
unnamed: U1.35 (X48P), Y1.3
